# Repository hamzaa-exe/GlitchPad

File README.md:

# GlitchPad 

### A compact gaming macropad built for fast inputs, RGB glow, and cyberpunk vibes.

---

##  Renders

##  What is GlitchPad?

**GlitchPad** is a custom gaming macropad built around the **Seeed XIAO RP2040**, **KMK firmware**, a rotary encoder, OLED display, and **20 SK6812 Mini-E RGB LEDs**.

It's designed mainly for FPS gaming, while still being fully customizable for other uses.

### Features

*  6 Cherry MX-compatible switches
*  EC11 rotary encoder
*  0.91" OLED display
*  20 × SK6812 Mini-E LEDs
*  XIAO RP2040
*  Custom 3D-printed case
*  Custom PCB
*  KMK firmware
*  Cyber-blue glitch lighting

---

##  Button Layout

```text
             SPACE       UP

             SHIFT      LEFT      DOWN      RIGHT
```

The rotary encoder is designed for quick number-based controls, such as switching between weapon slots in FPS games.

---

##  OLED + RGB

The OLED features a custom glitch-style animation, while the 20 SK6812 Mini-E LEDs provide a **cyber-blue pulse** aesthetic.

---

##  BOM

See the complete Bill of Materials here:

**[View BOM](./BOM.md)**

---

##  Tools

* **KiCad** — PCB & schematic
* **Fusion 360** — CAD & case
* **KMK + CircuitPython** — Firmware

---

##  Why GlitchPad?

I wanted to build a compact gaming controller while learning more about **PCB design, CAD, firmware, and hardware manufacturing**.

Six buttons. One encoder. Twenty LEDs.

**That's GlitchPad. **

---

##  Author

**Hamza Sohail**

Built for **Hack Club Hackpad**.

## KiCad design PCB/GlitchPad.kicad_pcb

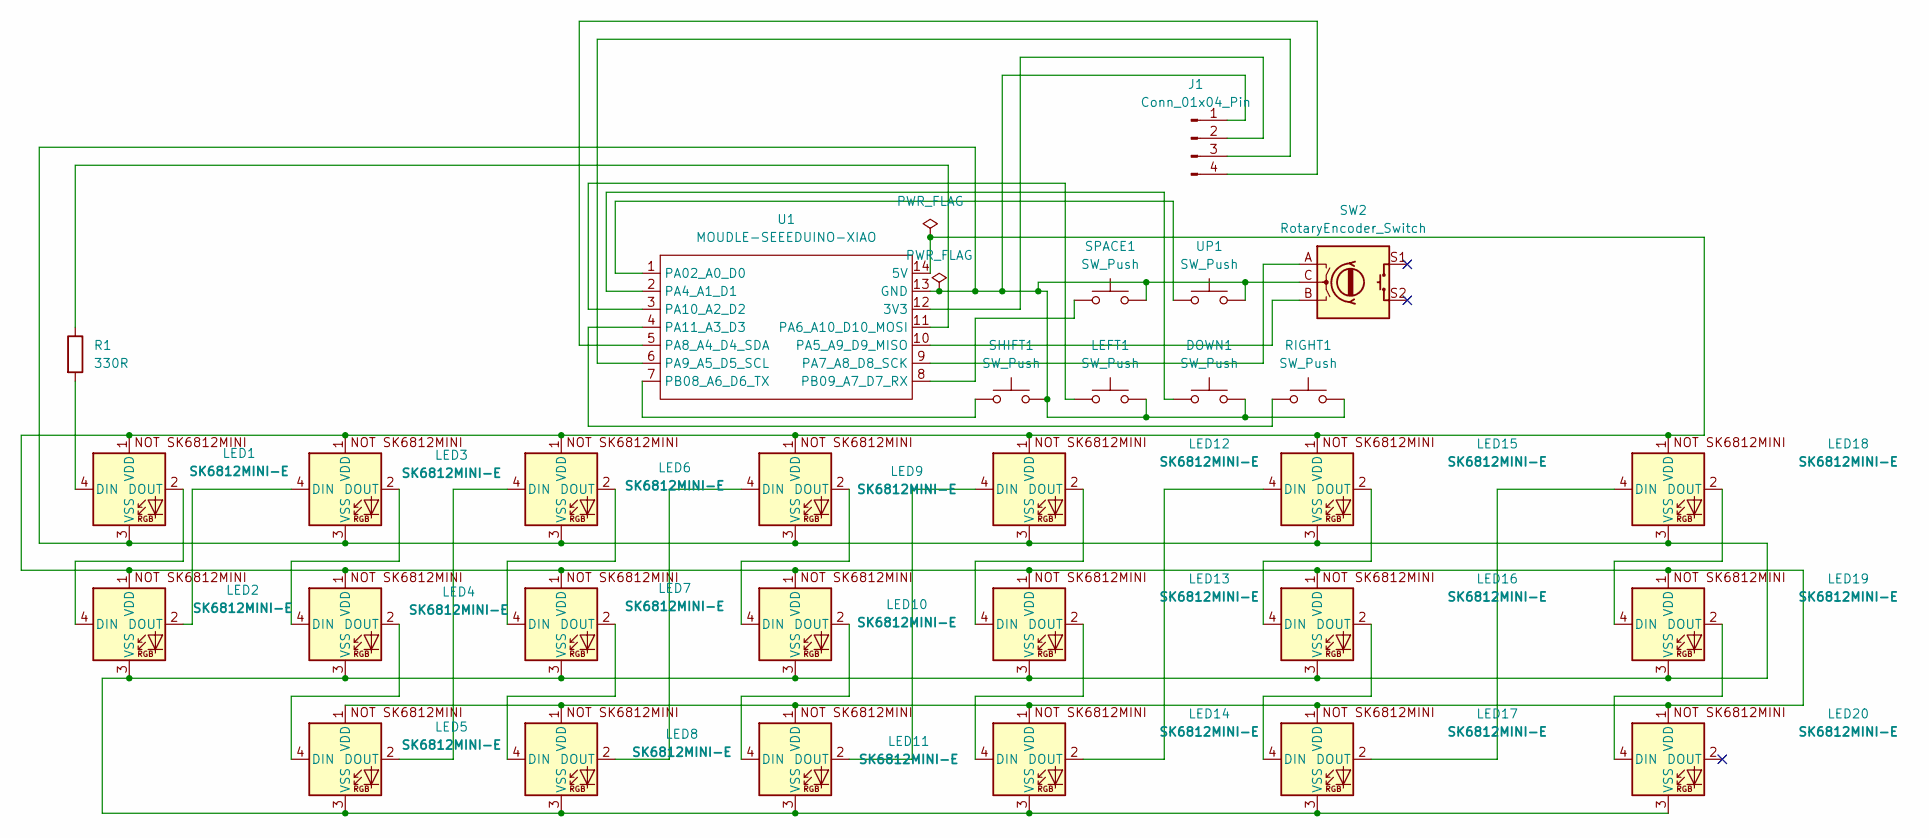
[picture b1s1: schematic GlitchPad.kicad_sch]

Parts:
DOWN1: SW_Push; SW_Cherry_MX_1.00u_PCB
J1: Conn_01x04_Pin; PinHeader_1x04_P2.54mm_Vertical
LED1, LED2, LED3, LED4, LED5, LED6, LED7, LED8, LED9, LED10, LED11, LED12, LED13, LED14, LED15, LED16, LED17, LED18, LED19, LED20: SK6812MINI-E; SK6812MINI-E_fixed
LEFT1: SW_Push; SW_Cherry_MX_1.00u_PCB
R1: 330R; R_Axial_DIN0207_L6.3mm_D2.5mm_P7.62mm_Horizontal
RIGHT1: SW_Push; SW_Cherry_MX_1.00u_PCB
SHIFT1: SW_Push; SW_Cherry_MX_1.00u_PCB
SPACE1: SW_Push; SW_Cherry_MX_1.00u_PCB
SW2: RotaryEncoder_Switch; RotaryEncoder_Alps_EC11E-Switch_Vertical_H20mm
U1: MOUDLE-SEEEDUINO-XIAO; XIAO-Generic-Hybrid-14P-2.54-21X17.8MM
UP1: SW_Push; SW_Cherry_MX_1.00u_PCB

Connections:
unnamed: DOWN1.2, J1.1, LED1.3 (VSS), LED2.3 (VSS), LED3.3 (VSS), LED4.3 (VSS), LED5.3 (VSS), LED6.3 (VSS), LED7.3 (VSS), LED8.3 (VSS), LED9.3 (VSS), LED10.3 (VSS), LED11.3 (VSS), LED12.3 (VSS), LED13.3 (VSS), LED14.3 (VSS), LED15.3 (VSS), LED16.3 (VSS), LED17.3 (VSS), LED18.3 (VSS), LED19.3 (VSS), LED20.3 (VSS), LEFT1.2, RIGHT1.2, SHIFT1.2, SPACE1.2, SW2.C, U1.13 (GND), UP1.2
unnamed: J1.2, U1.12 (3V3)
unnamed: J1.3, U1.6 (PA9_A5_D5_SCL)
unnamed: J1.4, U1.5 (PA8_A4_D4_SDA)
unnamed: LED1.4 (DIN), R1.2
unnamed: LED1.2 (DOUT), LED2.4 (DIN)
unnamed: LED1.1 (VDD), LED2.1 (VDD), LED3.1 (VDD), LED4.1 (VDD), LED5.1 (VDD), LED6.1 (VDD), LED7.1 (VDD), LED8.1 (VDD), LED9.1 (VDD), LED10.1 (VDD), LED11.1 (VDD), LED12.1 (VDD), LED13.1 (VDD), LED14.1 (VDD), LED15.1 (VDD), LED16.1 (VDD), LED17.1 (VDD), LED18.1 (VDD), LED19.1 (VDD), LED20.1 (VDD), U1.14 (5V)
unnamed: LED2.2 (DOUT), LED3.4 (DIN)
unnamed: LED3.2 (DOUT), LED4.4 (DIN)
unnamed: LED4.2 (DOUT), LED5.4 (DIN)
unnamed: LED5.2 (DOUT), LED6.4 (DIN)
unnamed: LED6.2 (DOUT), LED7.4 (DIN)
unnamed: LED7.2 (DOUT), LED8.4 (DIN)
unnamed: LED8.2 (DOUT), LED9.4 (DIN)
unnamed: LED9.2 (DOUT), LED10.4 (DIN)
unnamed: LED10.2 (DOUT), LED11.4 (DIN)
unnamed: LED11.2 (DOUT), LED12.4 (DIN)
unnamed: LED12.2 (DOUT), LED13.4 (DIN)
unnamed: LED13.2 (DOUT), LED14.4 (DIN)
unnamed: LED14.2 (DOUT), LED15.4 (DIN)
unnamed: LED15.2 (DOUT), LED16.4 (DIN)
unnamed: LED16.2 (DOUT), LED17.4 (DIN)
unnamed: LED17.2 (DOUT), LED18.4 (DIN)
unnamed: LED18.2 (DOUT), LED19.4 (DIN)
unnamed: LED19.2 (DOUT), LED20.4 (DIN)
unnamed: U1.1 (PA02_A0_D0), UP1.1
unnamed: DOWN1.1, U1.2 (PA4_A1_D1)
unnamed: SW2.B, U1.10 (PA5_A9_D9_MISO)
unnamed: R1.1, U1.11 (PA6_A10_D10_MOSI)
unnamed: SW2.A, U1.9 (PA7_A8_D8_SCK)
unnamed: LEFT1.1, U1.3 (PA10_A2_D2)
unnamed: RIGHT1.1, U1.4 (PA11_A3_D3)
unnamed: SHIFT1.1, U1.7 (PB08_A6_D6_TX)
unnamed: SPACE1.1, U1.8 (PB09_A7_D7_RX)

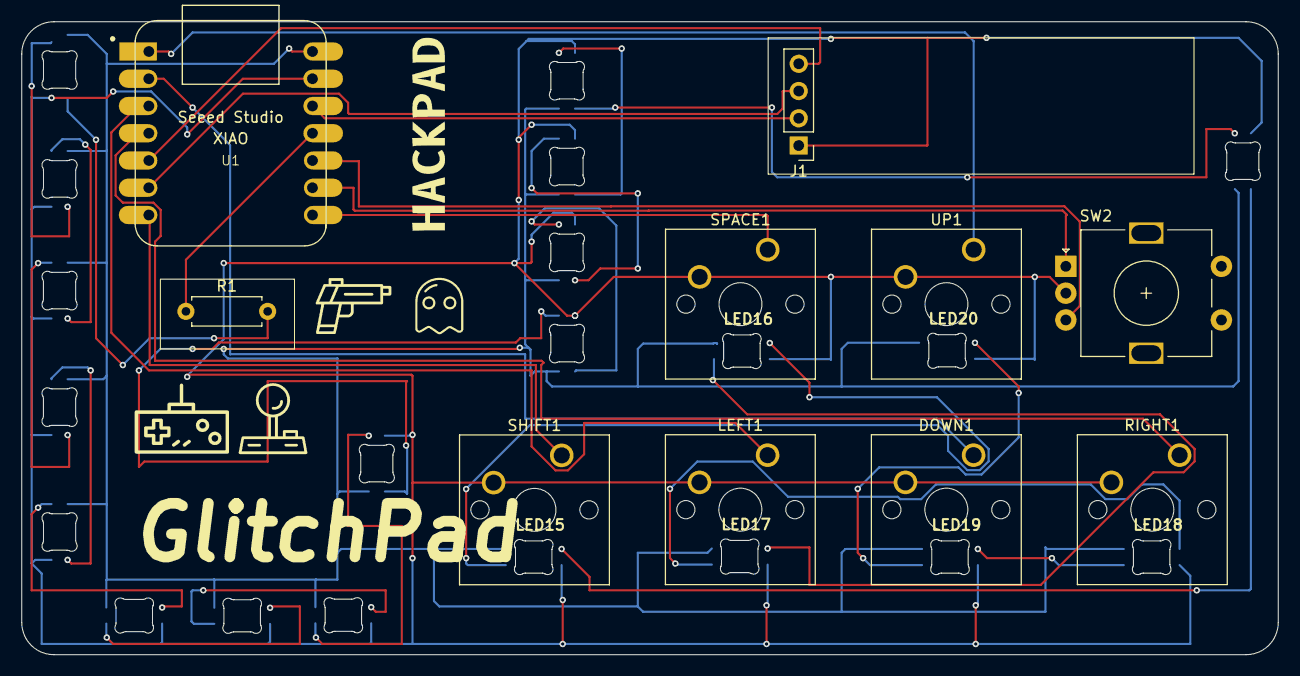
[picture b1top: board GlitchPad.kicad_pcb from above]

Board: 2 copper layers, 117.1 x 59.0 mm, 30 parts (0 on the bottom side), 34 nets.
